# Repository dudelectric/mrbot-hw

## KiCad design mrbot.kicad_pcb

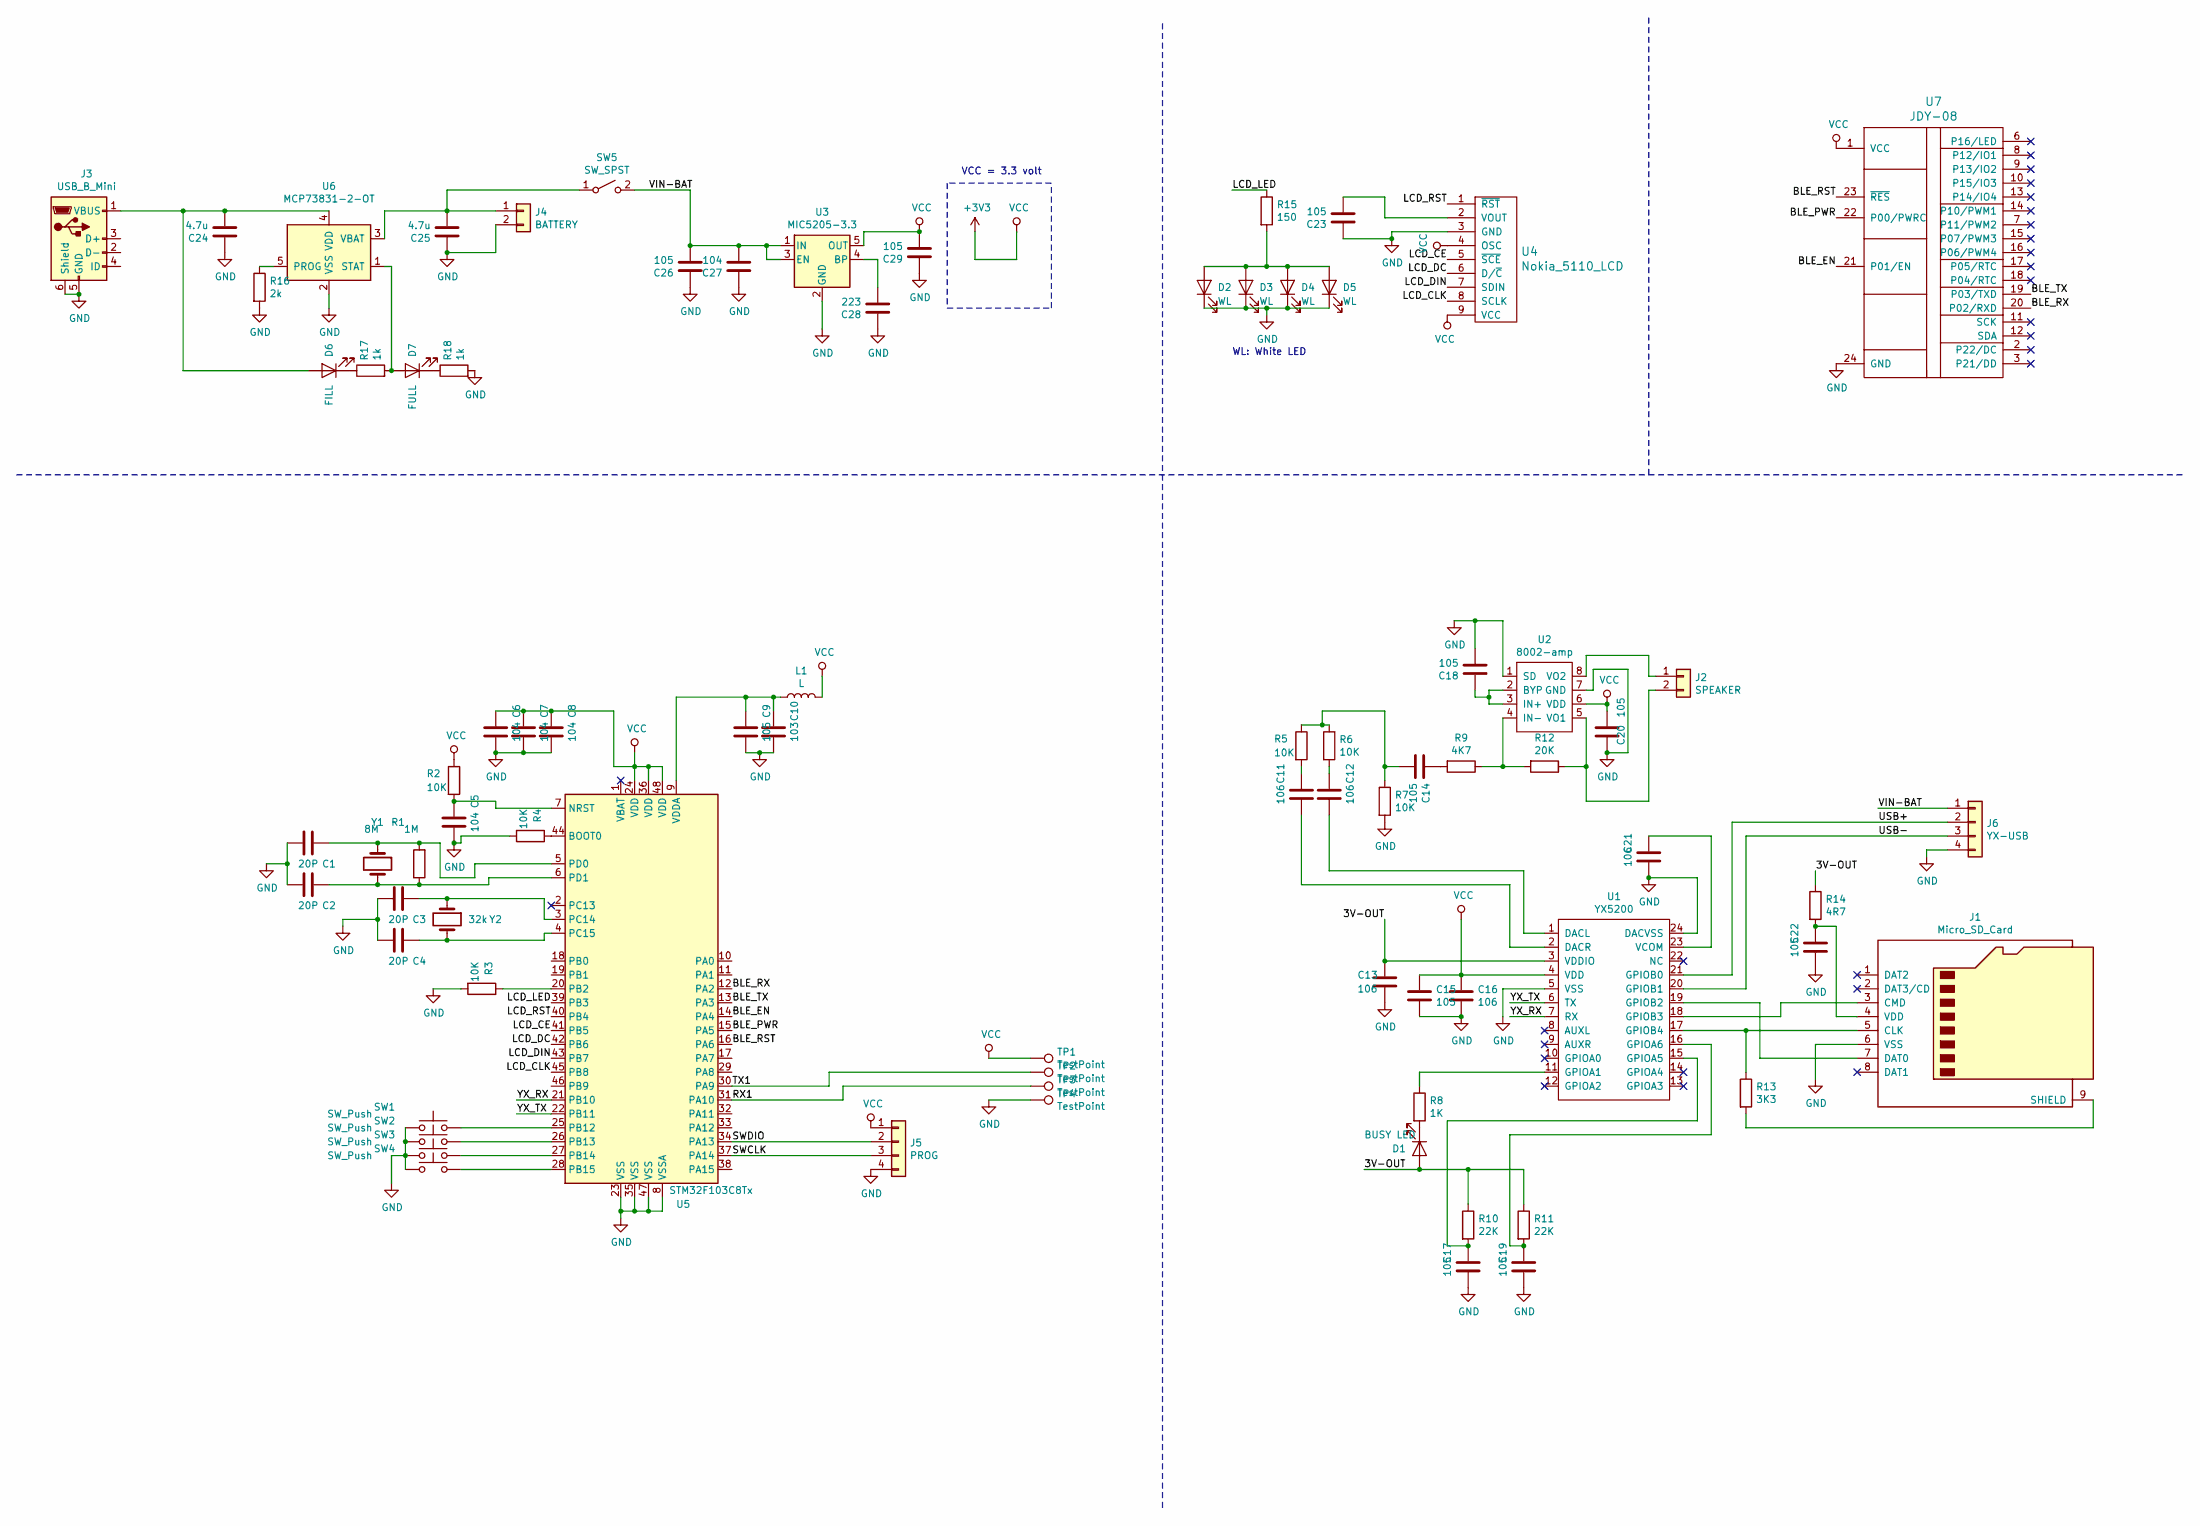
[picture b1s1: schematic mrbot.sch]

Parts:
C1, C2, C3, C4: 20P; C_0805_2012Metric_Pad1.15x1.40mm_HandSolder
C5, C6, C7, C8, C27: 104; C_0805_2012Metric_Pad1.15x1.40mm_HandSolder
C9, C14, C15, C17, C18, C19, C20, C22, C23, C26, C29: 105; C_0805_2012Metric_Pad1.15x1.40mm_HandSolder
C10: 103; C_0805_2012Metric_Pad1.15x1.40mm_HandSolder
C11, C12, C13, C16, C21: 106; C_0805_2012Metric_Pad1.15x1.40mm_HandSolder
C24, C25: 4.7u; C_0805_2012Metric_Pad1.15x1.40mm_HandSolder
C28: 223; C_0805_2012Metric_Pad1.15x1.40mm_HandSolder
D1: BUSY LED; LED_0805_2012Metric_Castellated
D2, D3, D4, D5: WL; LED_0805_2012Metric_Castellated
D6: FILL; LED_0805_2012Metric_Castellated
D7: FULL; LED_0805_2012Metric_Castellated
J1: Micro_SD_Card; GCT-MEM2055-00-190-01-A
J2: SPEAKER; JST_EH_B02B-EH-A_1x02_P2.50mm_Vertical
J3: USB_B_Mini; USB_Mini-B_Lumberg_2486_01_Horizontal
J4: BATTERY; JST_EH_B02B-EH-A_1x02_P2.50mm_Vertical
J5: PROG; PinHeader_1x04_P2.54mm_Vertical
J6: YX-USB; PinHeader_1x04_P2.54mm_Vertical
L1: L; L_0805_2012Metric_Pad1.15x1.40mm_HandSolder
R1: 1M; R_0805_2012Metric_Pad1.15x1.40mm_HandSolder
R2, R3, R4, R5, R6, R7: 10K; R_0805_2012Metric_Pad1.15x1.40mm_HandSolder
R8: 1K; R_0805_2012Metric_Pad1.15x1.40mm_HandSolder
R9: 4K7; R_0805_2012Metric_Pad1.15x1.40mm_HandSolder
R10, R11: 22K; R_0805_2012Metric_Pad1.15x1.40mm_HandSolder
R12: 20K; R_0805_2012Metric_Pad1.15x1.40mm_HandSolder
R13: 3K3; R_0805_2012Metric_Pad1.15x1.40mm_HandSolder
R14: 4R7; R_0805_2012Metric_Pad1.15x1.40mm_HandSolder
R15: 150; R_0805_2012Metric_Pad1.15x1.40mm_HandSolder
R16: 2k; R_0805_2012Metric_Pad1.15x1.40mm_HandSolder
R17, R18: 1k; R_0805_2012Metric_Pad1.15x1.40mm_HandSolder
SW1, SW2, SW3, SW4: SW_Push; SW_Tactile_SPST_Angled_PTS645Vx58-2LFS
SW5: SW_SPST; JST_EH_B02B-EH-A_1x02_P2.50mm_Vertical
TP1, TP2, TP3, TP4: TestPoint; TestPoint_Pad_1.5x1.5mm
U1: YX5200; SSOP-24_5.3x8.2mm_P0.65mm
U2: 8002-amp; SOIC-8_3.9x4.9mm_P1.27mm
U3: MIC5205-3.3; SOT-23-5
U4: Nokia_5110_LCD; Nokia_5110-3310_LCD-F.Paste-B.Paste
U5: STM32F103C8Tx; LQFP-48_7x7mm_P0.5mm
U6: MCP73831-2-OT; SOT-23-5
U7: JDY-08; JDY-08_HandSoldering
Y1: 8M; Crystal_HC49-4H_Vertical
Y2: 32k; Crystal_SMD_7050-4Pin_7.0x5.0mm

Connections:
+3V3: C6.2, C7.2, C8.2, C15.2, C16.2, C20.2, C29.1, J5.1, L1.2, R2.1, TP1.1, U1.4 (VDD), U2.6 (VDD), U3.5 (OUT), U4.4 (OSC), U4.9 (VCC), U5.24 (VDD), U5.36 (VDD), U5.48 (VDD), U7.1 (VCC); also elsewhere on the board
/3V-OUT: C13.2, D1.2 (A), R10.1, R11.1, R14.1, U1.3 (VDDIO)
/BLE_EN: U5.14 (PA4), U7.21 (P01/EN)
/BLE_PWR: U5.15 (PA5), U7.22 (P00/PWRC)
/BLE_RST: U5.16 (PA6), U7.23 (~RES)
/BLE_RX: U5.12 (PA2), U7.20 (P02/RXD)
/BLE_TX: U5.13 (PA3), U7.19 (P03/TXD)
/LCD_CE: U4.5 (~SCE), U5.41 (PB5)
/LCD_CLK: U4.8 (SCLK), U5.45 (PB8)
/LCD_DC: U4.6 (D/~C), U5.42 (PB6)
/LCD_DIN: U4.7 (SDIN), U5.43 (PB7)
/LCD_LED: R15.1, U5.39 (PB3)
/LCD_RST: U4.1 (~RST), U5.40 (PB4)
/RX1: TP3.1, U5.31 (PA10); also elsewhere on the board
/SWCLK: J5.3, U5.37 (PA14)
/SWDIO: J5.2, U5.34 (PA13)
/TX1: TP2.1, U5.30 (PA9); also elsewhere on the board
/USB+: J6.2, U1.21 (GPIOB0)
/USB-: J6.3, U1.20 (GPIOB1)
/VIN-BAT: C26.1, C27.1, J6.1, SW5.2 (B), U3.1 (IN), U3.3 (EN)
/YX_RX: U1.7 (RX), U5.21 (PB10)
/YX_TX: U1.6 (TX), U5.22 (PB11)
GND: C1.1, C2.1, C3.1, C4.1, C5.1, C6.1, C7.1, C8.1, C9.1, C10.1, C13.1, C15.1, C16.1, C17.1, C18.1, C19.1, C20.1, C21.1, C22.1, C23.2, C24.2, C25.2, C26.2, C27.2, C28.2, C29.2, D2.1 (K), D3.1 (K), D4.1 (K), D5.1 (K), J1.6 (VSS), J3.5 (GND), J3.6 (Shield), J4.2, J5.4, J6.4, R3.2, R4.2, R7.2, R16.2, R18.2, SW1.1, SW2.1, SW3.1, SW4.1, TP4.1, U1.5 (VSS), U1.24 (DACVSS), U2.1 (SD), U2.7 (GND), U3.2 (GND), U4.3 (GND), U5.8 (VSSA), U5.23 (VSS), U5.35 (VSS), U5.47 (VSS), U6.2 (VSS), U7.24 (GND); also elsewhere on the board
unnamed: C1.2, R1.2, U5.5 (PD0), Y1.1
unnamed: C2.2, R1.1, U5.6 (PD1), Y1.2
unnamed: C3.2, U5.3 (PC14), Y2.1
unnamed: C4.2, U5.4 (PC15), Y2.2
unnamed: C5.2, R2.2, U5.7 (NRST)
unnamed: C9.2, C10.2, L1.1, U5.9 (VDDA)
unnamed: C11.1, U1.2 (DACR)
unnamed: C11.2, R5.2
unnamed: C12.1, U1.1 (DACL)
unnamed: C12.2, R6.2
unnamed: C14.1, R5.1, R6.1, R7.1
unnamed: C14.2, R9.2
unnamed: C17.2, R10.2, U1.15 (GPIOA5)
unnamed: C18.2, U2.2 (BYP), U2.3 (IN+)
unnamed: C19.2, R11.2, U1.16 (GPIOA6)
unnamed: C21.2, U1.23 (VCOM)
unnamed: C22.2, J1.4 (VDD), R14.2
unnamed: C23.1, U4.2 (VOUT)
unnamed: C24.1, D6.2 (A), J3.1 (VBUS), U6.4 (VDD)
unnamed: C25.1, J4.1, SW5.1 (A), U6.3 (VBAT)
unnamed: C28.1, U3.4 (BP)
unnamed: D1.1 (K), R8.2
unnamed: D2.2 (A), D3.2 (A), D4.2 (A), D5.2 (A), R15.2
unnamed: D6.1 (K), R17.1
unnamed: D7.1 (K), R18.1
unnamed: D7.2 (A), R17.2, U6.1 (STAT)
unnamed: J1.3 (CMD), U1.18 (GPIOB3)
unnamed: J1.5 (CLK), R13.1, U1.17 (GPIOB4)
unnamed: J1.7 (DAT0), U1.19 (GPIOB2)
unnamed: J1.9 (SHIELD), R13.2
unnamed: J2.1, U2.8 (VO2)
unnamed: J2.2, R12.1, U2.5 (VO1)
unnamed: R3.1, U5.20 (PB2)
unnamed: R4.1, U5.44 (BOOT0)
unnamed: R8.1, U1.11 (GPIOA1)
unnamed: R9.1, R12.2, U2.4 (IN-)
unnamed: R16.1, U6.5 (PROG)
unnamed: SW1.2, U5.25 (PB12)
unnamed: SW2.2, U5.26 (PB13)
unnamed: SW3.2, U5.27 (PB14)
unnamed: SW4.2, U5.28 (PB15)

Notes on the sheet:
VCC = 3.3 volt
WL: White LED

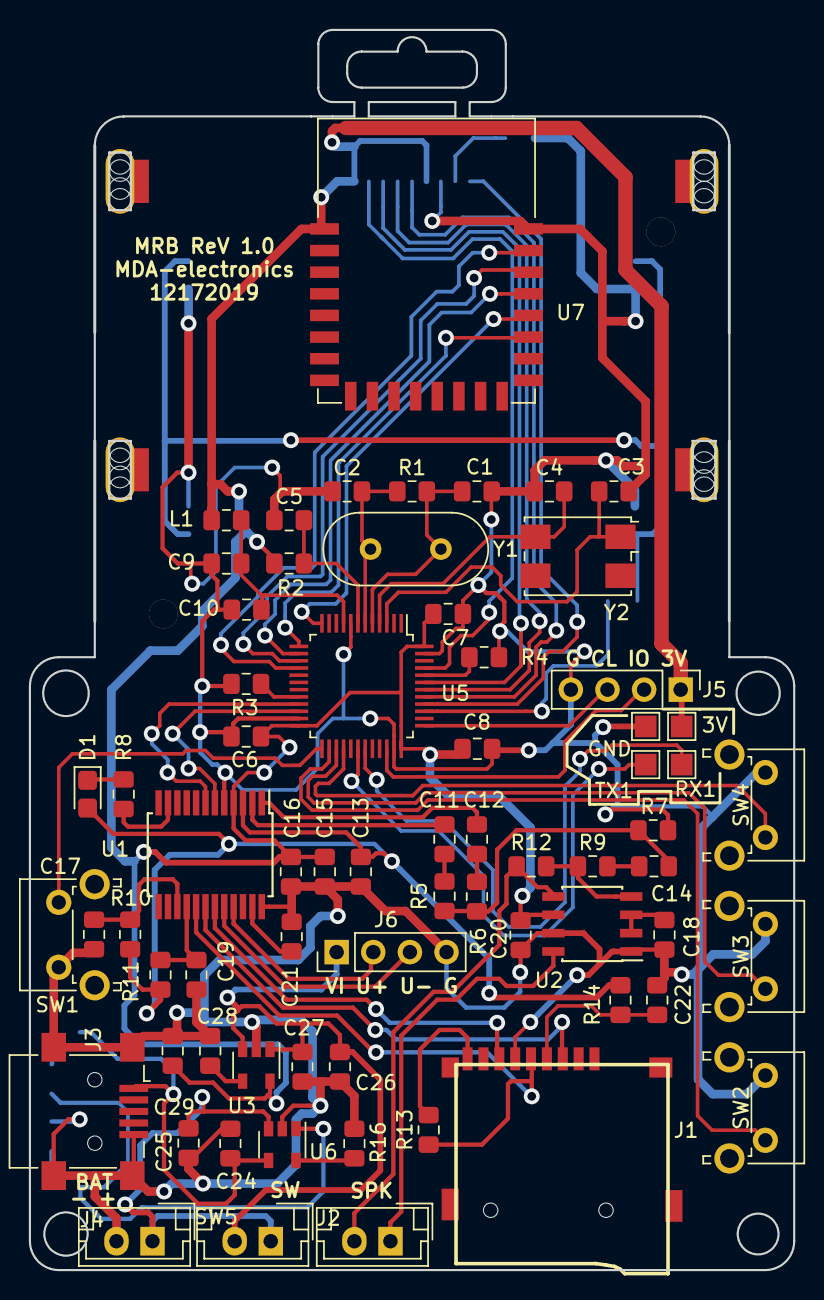
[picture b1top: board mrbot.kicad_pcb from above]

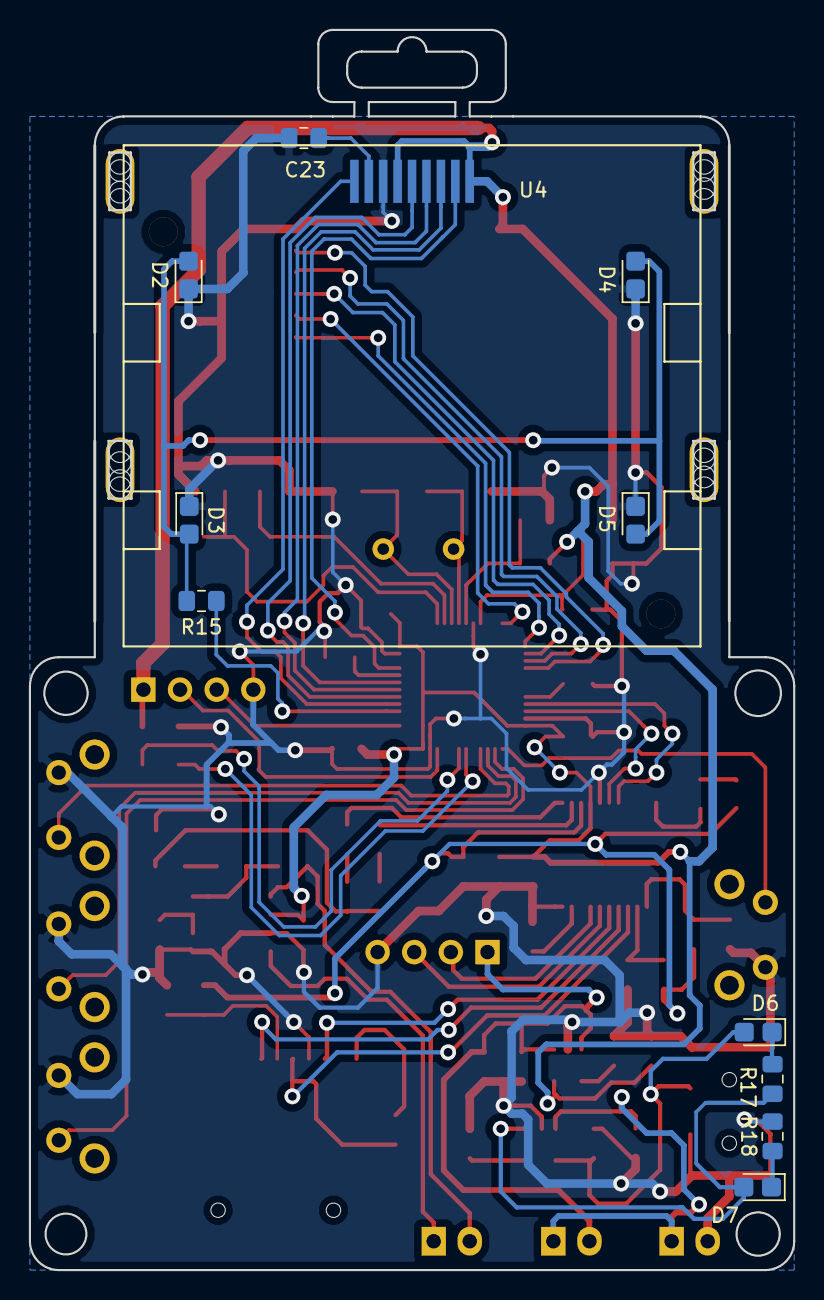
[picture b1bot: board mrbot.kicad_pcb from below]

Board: 2 copper layers, 53.0 x 86.0 mm, 79 parts (11 on the bottom side), 64 nets.

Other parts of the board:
3V: TestPoint; TestPoint_Pad_1.5x1.5mm
GND: TestPoint; TestPoint_Pad_1.5x1.5mm
RX1: TestPoint; TestPoint_Pad_1.5x1.5mm
TX1: TestPoint; TestPoint_Pad_1.5x1.5mm

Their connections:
+3V3: 3V.1; also elsewhere on the board
/RX1: RX1.1; also elsewhere on the board
/TX1: TX1.1; also elsewhere on the board
GND: GND.1; also elsewhere on the board

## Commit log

2020-01-23 initial
